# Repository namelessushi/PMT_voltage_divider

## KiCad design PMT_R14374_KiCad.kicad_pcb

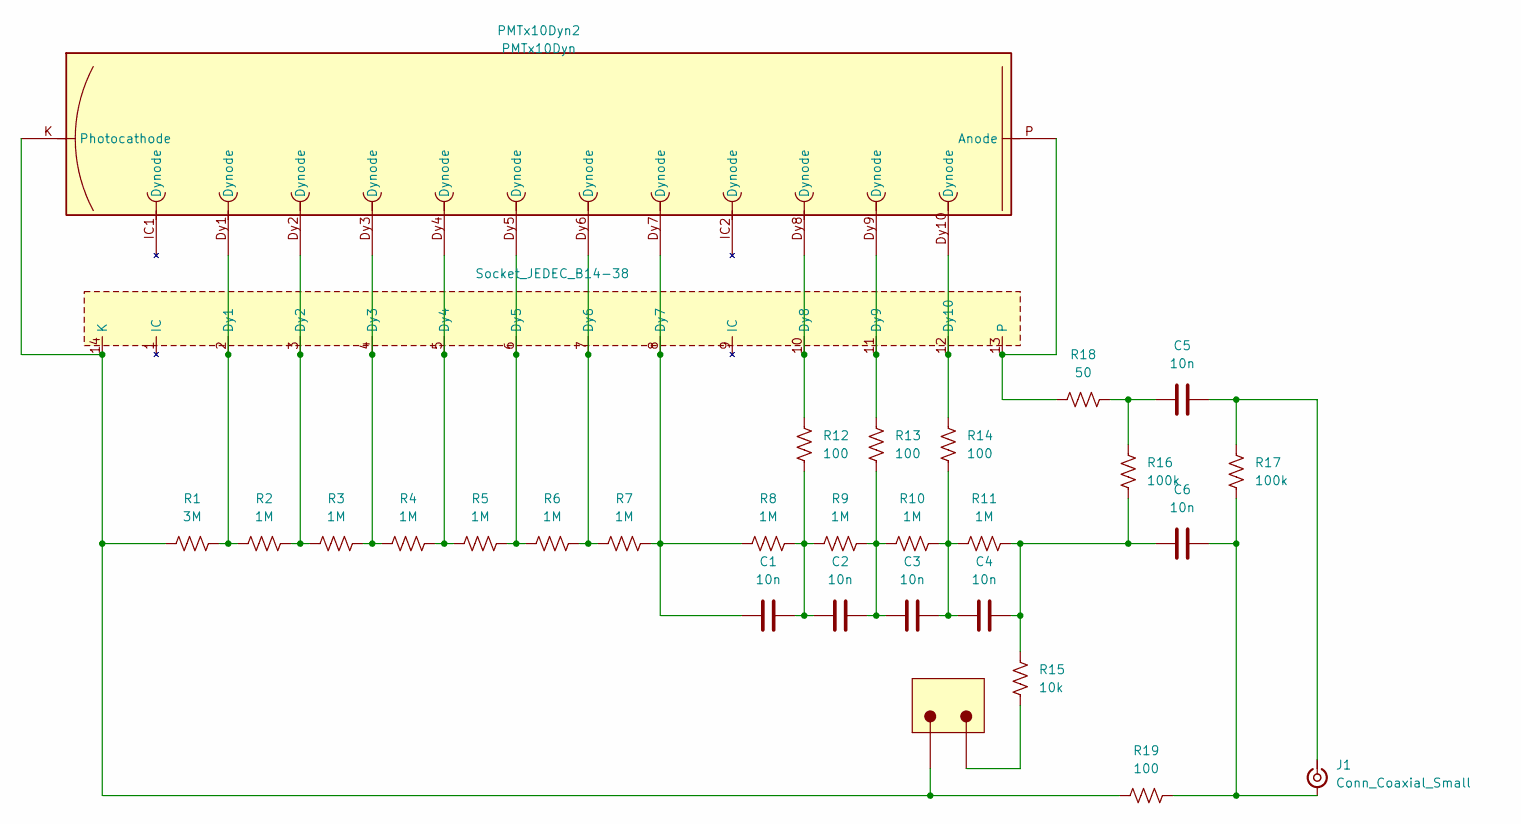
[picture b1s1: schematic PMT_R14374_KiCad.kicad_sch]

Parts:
C1, C2, C3, C4, C5, C6: 10n; Capacitor_THT_PMT
J1: Conn_Coaxial_Small; SMA_Amphenol_901-144_Vertical
JST_1-x-1/3-pin1: -; JST_B3B-ZR(LF)(SN); Part Number JST_B3B-ZR(LF)(SN)
PMTx10Dyn2: PMTx10Dyn
R1: 3M; Resistencia_THT_PMT
R2, R3, R4, R5, R6, R7, R8, R9, R10, R11: 1M; Resistencia_THT_PMT
R12, R13, R14, R19: 100; Resistencia_THT_PMT
R15: 10k; Resistencia_THT_PMT
R16, R17: 100k; Resistencia_THT_PMT
R18: 50; Resistencia_THT_PMT
Socket_JEDEC_B14-38: Socket-JEDEC

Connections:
unnamed: C1.2, C2.1, R8.2, R9.1, R12.2
unnamed: C2.2, C3.2, R9.2, R10.1, R13.2
unnamed: C3.1, C4.2, R10.2, R11.1, R14.2
unnamed: C4.1, C6.1, R11.2, R15.1, R16.2
unnamed: C5.1, R16.1, R18.2
unnamed: C6.2, J1.2 (Ext), R17.2, R19.2
unnamed: C5.2, J1.1 (In), R17.1
unnamed: JST_1-x-1/3-pin1.2, R15.2
unnamed: PMTx10Dyn2.Dy1 (Dynode), R1.1, R2.1, Socket_JEDEC_B14-38.2 (Dy1)
unnamed: PMTx10Dyn2.Dy2 (Dynode), R2.2, R3.1, Socket_JEDEC_B14-38.3 (Dy2)
unnamed: PMTx10Dyn2.Dy3 (Dynode), R3.2, R4.1, Socket_JEDEC_B14-38.4 (Dy3)
unnamed: PMTx10Dyn2.Dy4 (Dynode), R4.2, R5.1, Socket_JEDEC_B14-38.5 (Dy4)
unnamed: PMTx10Dyn2.Dy5 (Dynode), R5.2, R6.1, Socket_JEDEC_B14-38.6 (Dy5)
unnamed: PMTx10Dyn2.Dy6 (Dynode), R6.2, R7.1, Socket_JEDEC_B14-38.7 (Dy6)
unnamed: C1.1, PMTx10Dyn2.Dy7 (Dynode), R7.2, R8.1, Socket_JEDEC_B14-38.8 (Dy7)
unnamed: PMTx10Dyn2.Dy8 (Dynode), R12.1, Socket_JEDEC_B14-38.10 (Dy8)
unnamed: PMTx10Dyn2.Dy9 (Dynode), R13.1, Socket_JEDEC_B14-38.11 (Dy9)
unnamed: PMTx10Dyn2.Dy10 (Dynode), R14.1, Socket_JEDEC_B14-38.12 (Dy10)
unnamed: JST_1-x-1/3-pin1.1, PMTx10Dyn2.K (Photocathode), R1.2, R19.1, Socket_JEDEC_B14-38.14 (K)
unnamed: PMTx10Dyn2.P (Anode), R18.1, Socket_JEDEC_B14-38.13

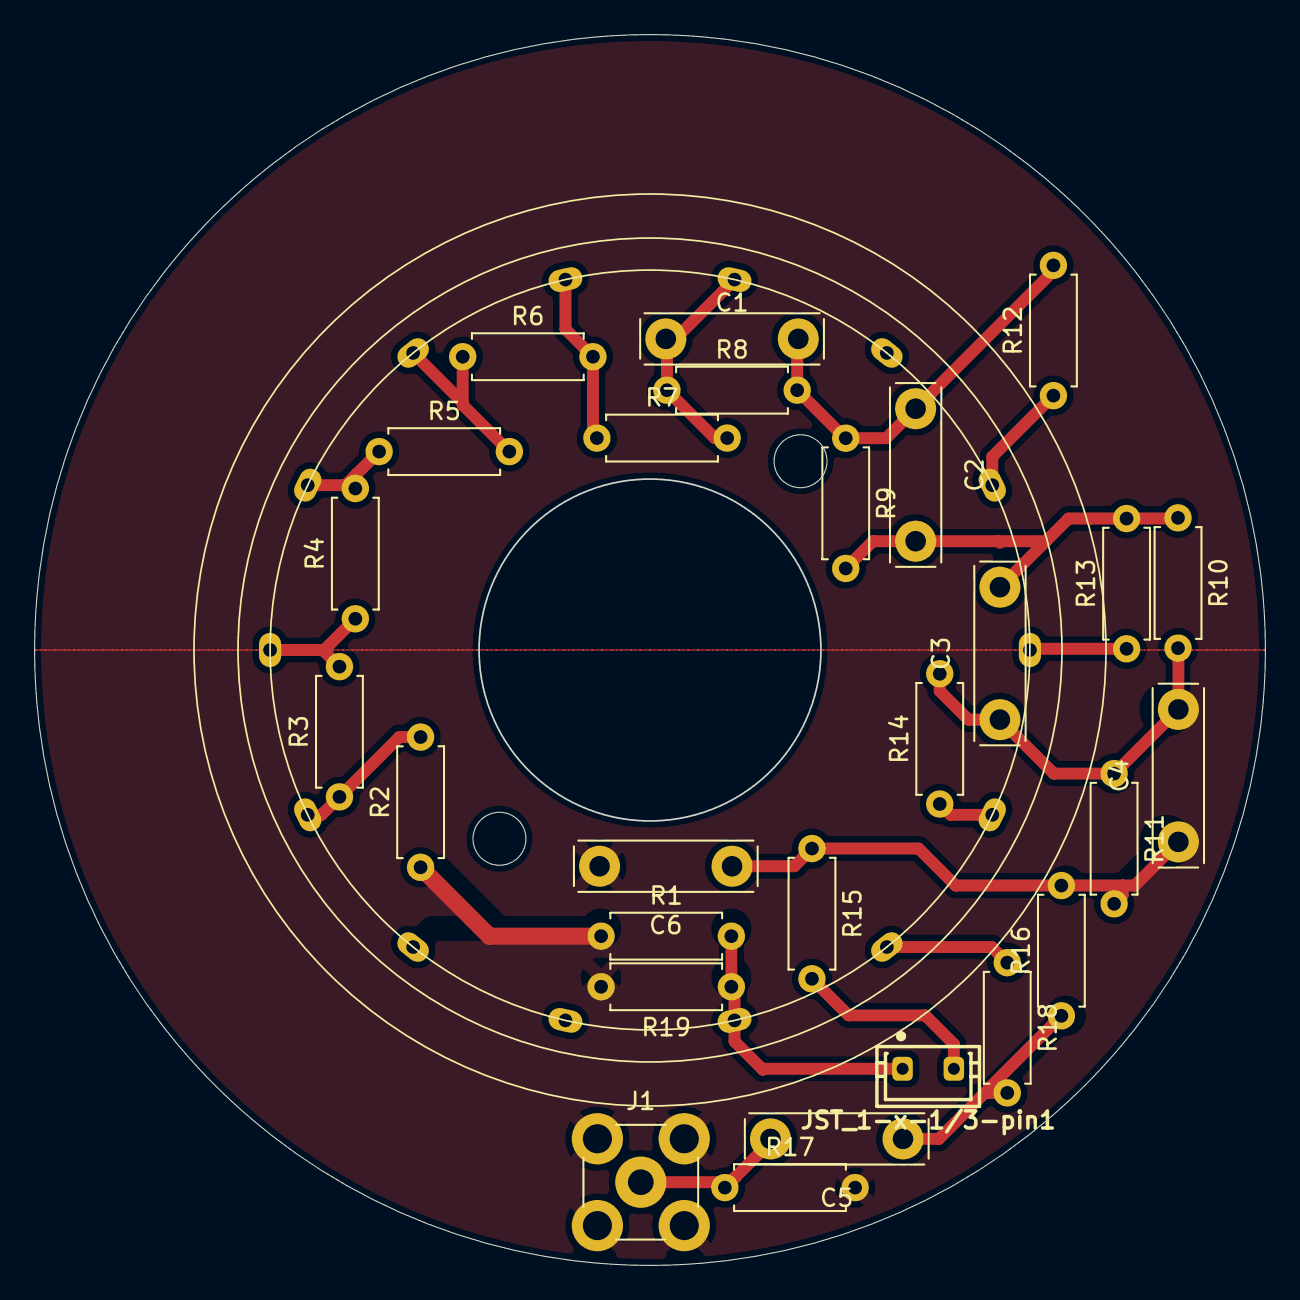
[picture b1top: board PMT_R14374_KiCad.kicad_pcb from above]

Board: 2 copper layers, 72.0 x 72.0 mm, 28 parts (0 on the bottom side), 20 nets.
